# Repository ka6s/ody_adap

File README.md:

# Odyssey-II adapter
This is a break out board for the Oddyssey II HPSDR transceiver.

I have done a couple of versions of this - the final configuration has a SPI output, but also
expects to be able to support a x4 HERMES style filter set up.  There is also a custom 
connector on here to drive the companion antenna switch. Note that there is only ONE 
ANT output available - so only two antenna ports are supported.

Lots of copies of PTT-out..can't have too many of those!

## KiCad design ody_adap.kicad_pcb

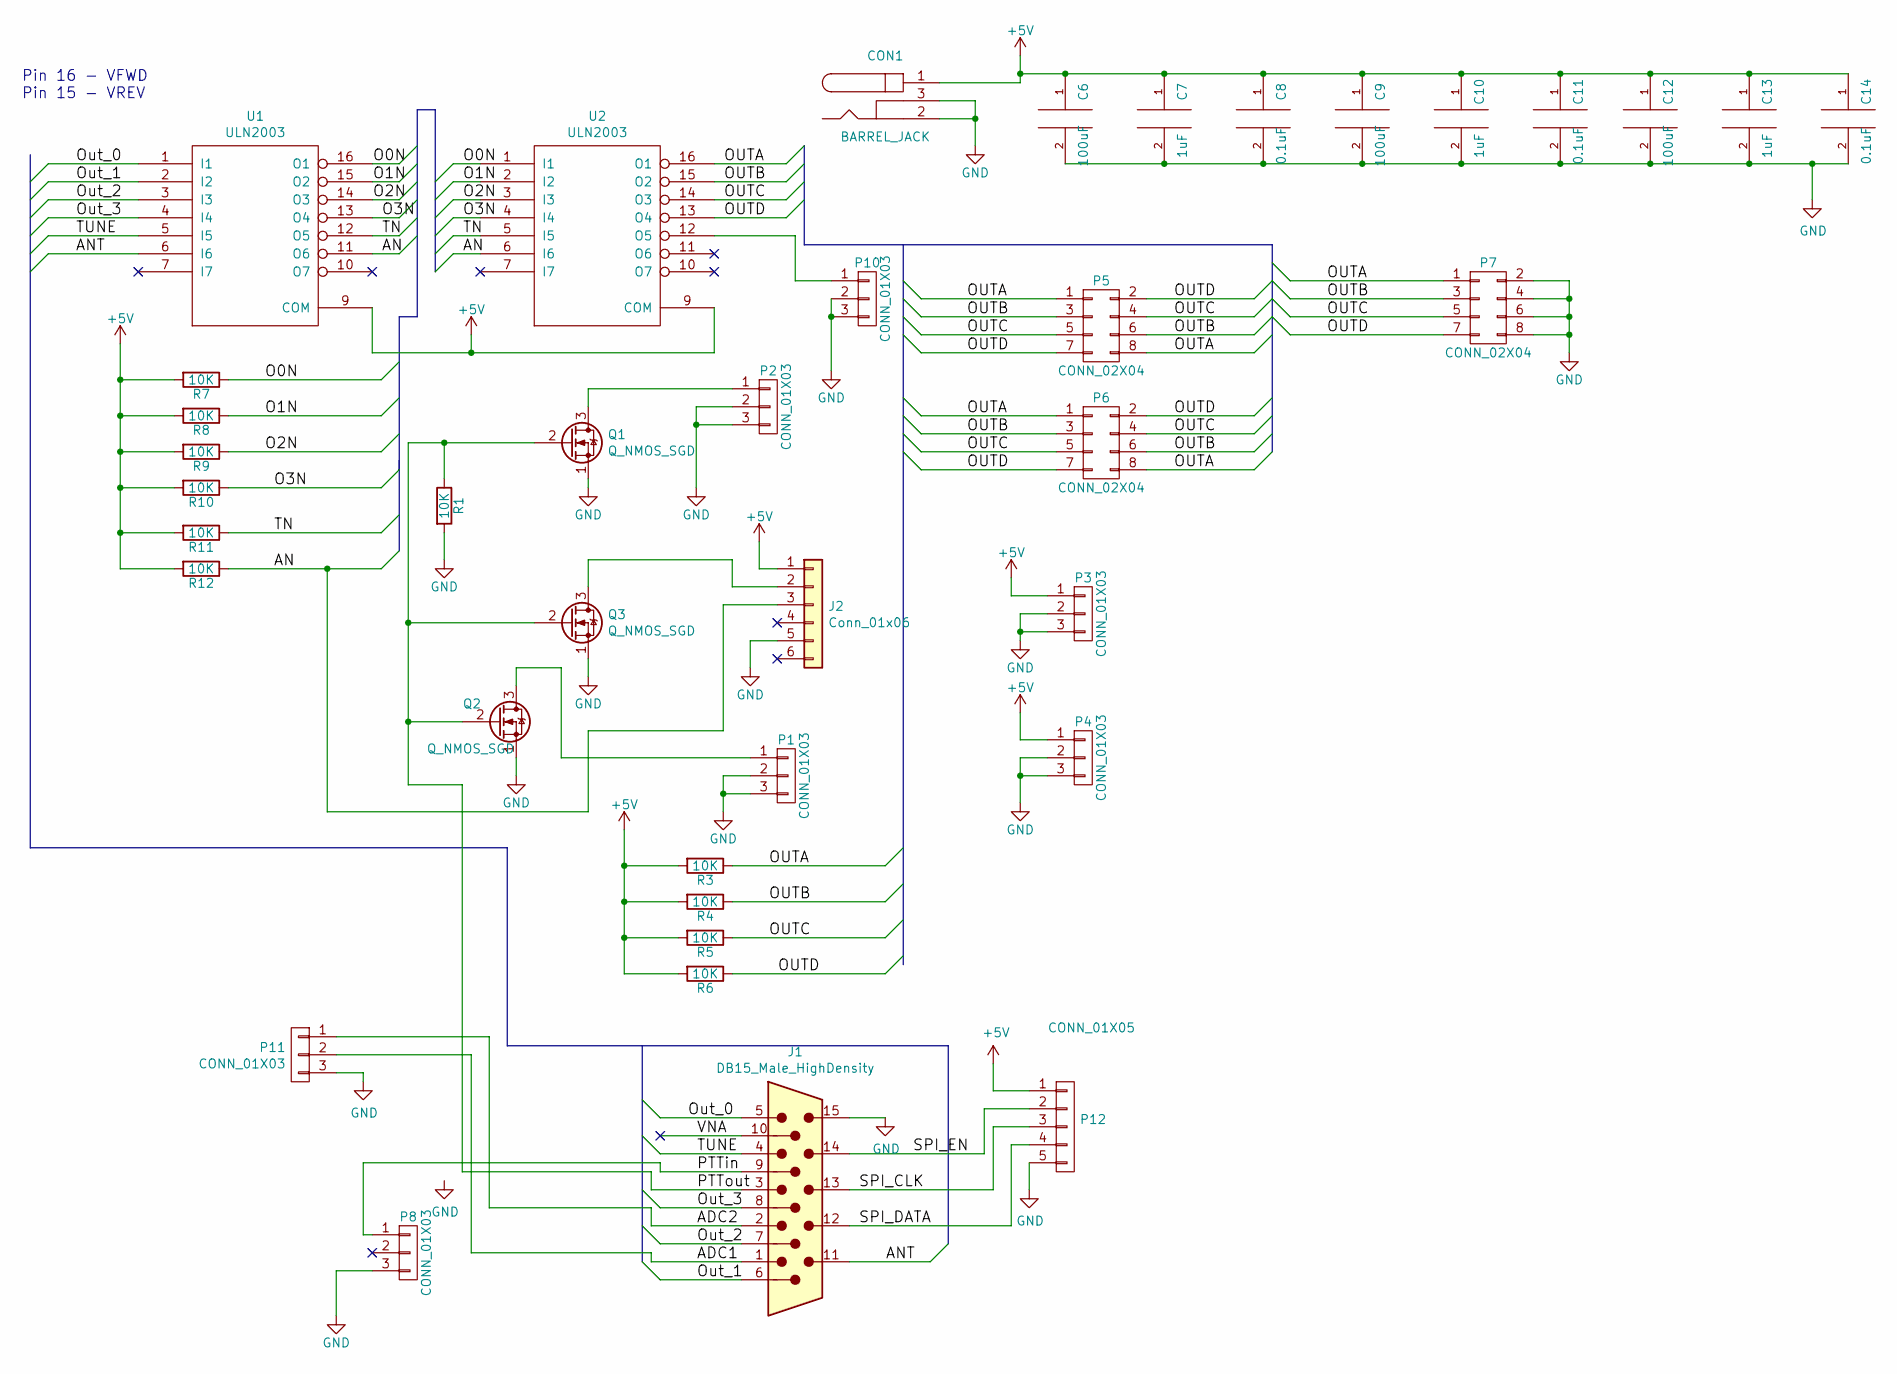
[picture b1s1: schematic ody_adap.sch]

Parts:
C6, C9, C12: 100uF; C_1210_HandSoldering
C7, C10, C13: 1uF; C_1210_HandSoldering
C8, C11: 0.1uF; C_1206_HandSoldering
C14: 0.1uF; C_1206
CON1: BARREL_JACK
J1: DB15_Male_HighDensity
J2: Conn_01x06; Pin_Header_Straight_1x06_Pitch2.54mm
P1, P2, P3, P4, P8, P10: CONN_01X03; Pin_Header_Straight_1x03
P5, P6, P7: CONN_02X04; Pin_Header_Straight_2x04
P11: CONN_01X03; Pin_Header_Straight_1x03_Pitch2.54mm
P12: CONN_01X05; Pin_Header_Straight_1x05_Pitch2.54mm
Q1, Q2, Q3: Q_NMOS_SGD; TO-92_Molded_Narrow
R1, R3, R4, R5, R6, R7, R8, R9, R10, R11, R12: 10K; R_1206_HandSoldering
U1, U2: ULN2003; DIP-16_W7.62mm

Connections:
+5V: C6.1, C7.1, C8.1, C9.1, C10.1, C11.1, C12.1, C13.1, C14.1, CON1.1, J2.1, P3.1, P4.1, P12.1, R3.2, R4.2, R5.2, R6.2, R7.2, R8.2, R9.2, R10.2, R11.2, R12.2, U1.9 (COM), U2.9 (COM)
/ADC1: J1.1, P11.2
/ADC2: J1.2, P11.1
/AN: J2.3, R12.1, U1.11 (O6), U2.6 (I6)
/ANT: J1.11, U1.6 (I6)
/O0N: R7.1, U1.16 (O1), U2.1 (I1)
/O1N: R8.1, U1.15 (O2), U2.2 (I2)
/O2N: R9.1, U1.14 (O3), U2.3 (I3)
/O3N: R10.1, U1.13 (O4), U2.4 (I4)
/OUTA: P5.1, P5.8, P6.1, P6.8, P7.1, R3.1, U2.16 (O1)
/OUTB: P5.3, P5.6, P6.3, P6.6, P7.3, R4.1, U2.15 (O2)
/OUTC: P5.4, P5.5, P6.4, P6.5, P7.5, R5.1, U2.14 (O3)
/OUTD: P5.2, P5.7, P6.2, P6.7, P7.7, R6.1, U2.13 (O4)
/Out_0: J1.5, U1.1 (I1)
/Out_1: J1.6, U1.2 (I2)
/Out_2: J1.7, U1.3 (I3)
/Out_3: J1.8, U1.4 (I4)
/PTTin: J1.9, P8.1
/PTTout: J1.3, Q1.2 (G), Q2.2 (G), Q3.2 (G), R1.1
/SPI_CLK: J1.13, P12.3
/SPI_DATA: J1.12, P12.4
/SPI_EN: J1.14, P12.2
/TN: R11.1, U1.12 (O5), U2.5 (I5)
/TUNE: J1.4, U1.5 (I5)
/VNA: J1.10
GND: C6.2, C7.2, C8.2, C9.2, C10.2, C11.2, C12.2, C13.2, C14.2, CON1.2, CON1.3, J1.15, J2.5, P1.2, P1.3, P2.2, P2.3, P3.2, P3.3, P4.2, P4.3, P7.2, P7.4, P7.6, P7.8, P8.3, P10.2, P10.3, P11.3, P12.5, Q1.1 (S), Q2.1 (S), Q3.1 (S), R1.2, U1.8 (GND), U2.8 (GND); also elsewhere on the board
unnamed: J2.2, Q3.3 (D)
unnamed: P1.1, Q2.3 (D)
unnamed: P2.1, Q1.3 (D)
unnamed: P10.1, U2.12 (O5)

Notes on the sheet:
Pin 16 - VFWD Pin 15 - VREV

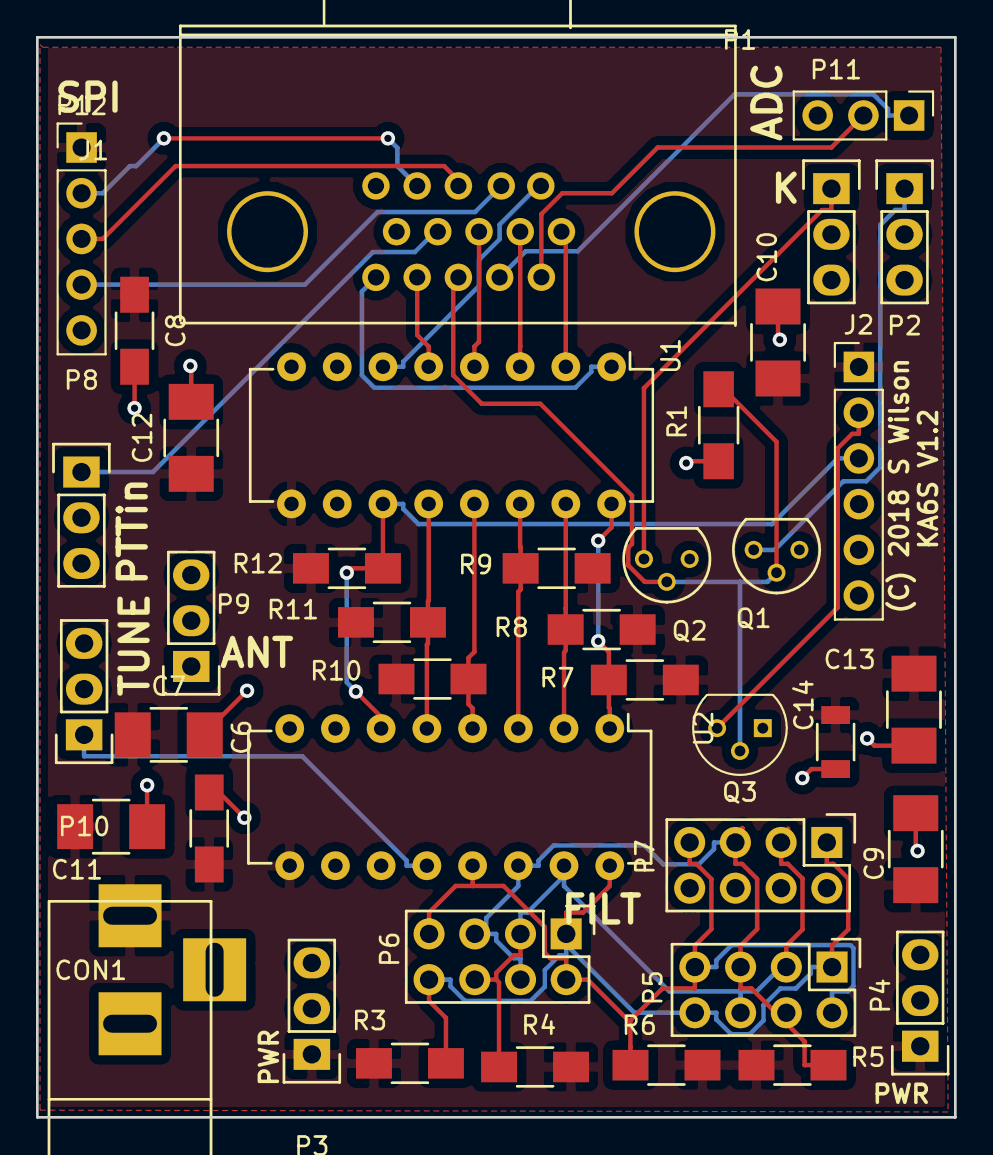
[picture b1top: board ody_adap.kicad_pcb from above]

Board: 2 copper layers, 51.0 x 60.0 mm, 40 parts (0 on the bottom side), 29 nets.

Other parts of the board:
P9: CONN_01X03; Pin_Header_Straight_1x03

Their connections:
GND: P9.3; also elsewhere on the board

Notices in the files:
ody_adap.kicad_pcb:
(C) 2018 S Wilson
